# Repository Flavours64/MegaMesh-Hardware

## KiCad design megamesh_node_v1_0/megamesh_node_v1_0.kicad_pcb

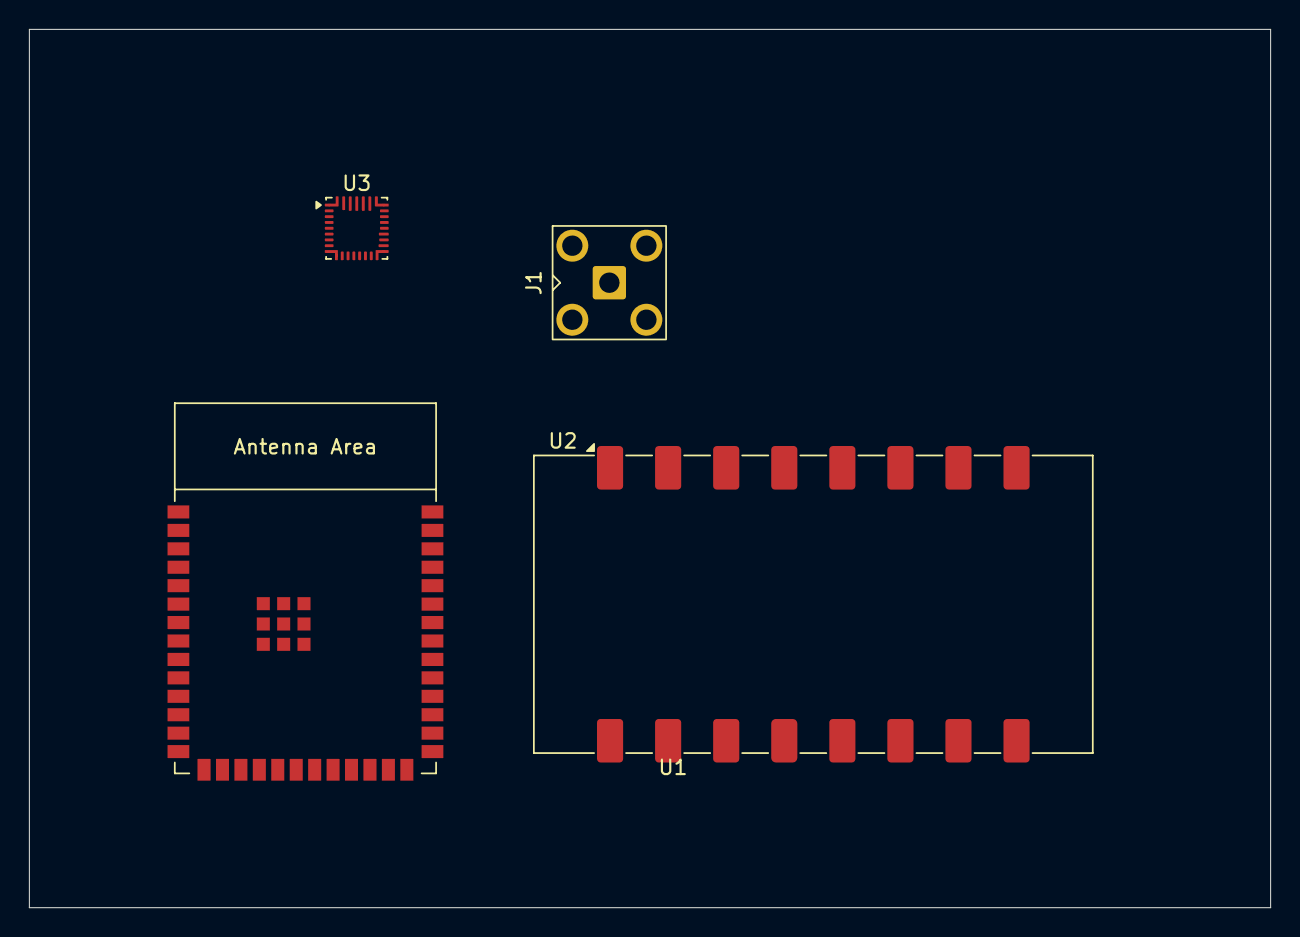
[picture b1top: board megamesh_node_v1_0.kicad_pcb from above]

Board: 2 copper layers, 85.5 x 60.5 mm, 4 parts (0 on the bottom side), 4 nets, no tracks yet.

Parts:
J1: Conn_Coaxial; SMA_BAT_Wireless_BWSMA-KWE-Z001
U1: ESP32-S3-WROOM-1
U2: LoRa126XF30
U3: BQ25798; Texas_RQM0029A_VQFN-29_4x4mm_P0.4mm

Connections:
GND: J1.2 (Ext), U1.1 (GND), U1.40 (GND), U1.41 (GND), U2.2 (GND), U2.15 (GND), U3.27 (GND)
unnamed: J1.1 (In), U2.16 (ANT)
unnamed: U3.22 (BAT), U3.23 (BAT)
unnamed: U3.2 (VBUS), U3.3 (VBUS)

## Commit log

2026-02-25 KiCad Projektdateien
